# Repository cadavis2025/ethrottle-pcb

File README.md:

## FALSTAD Link
https://tinyurl.com/2aynfxed

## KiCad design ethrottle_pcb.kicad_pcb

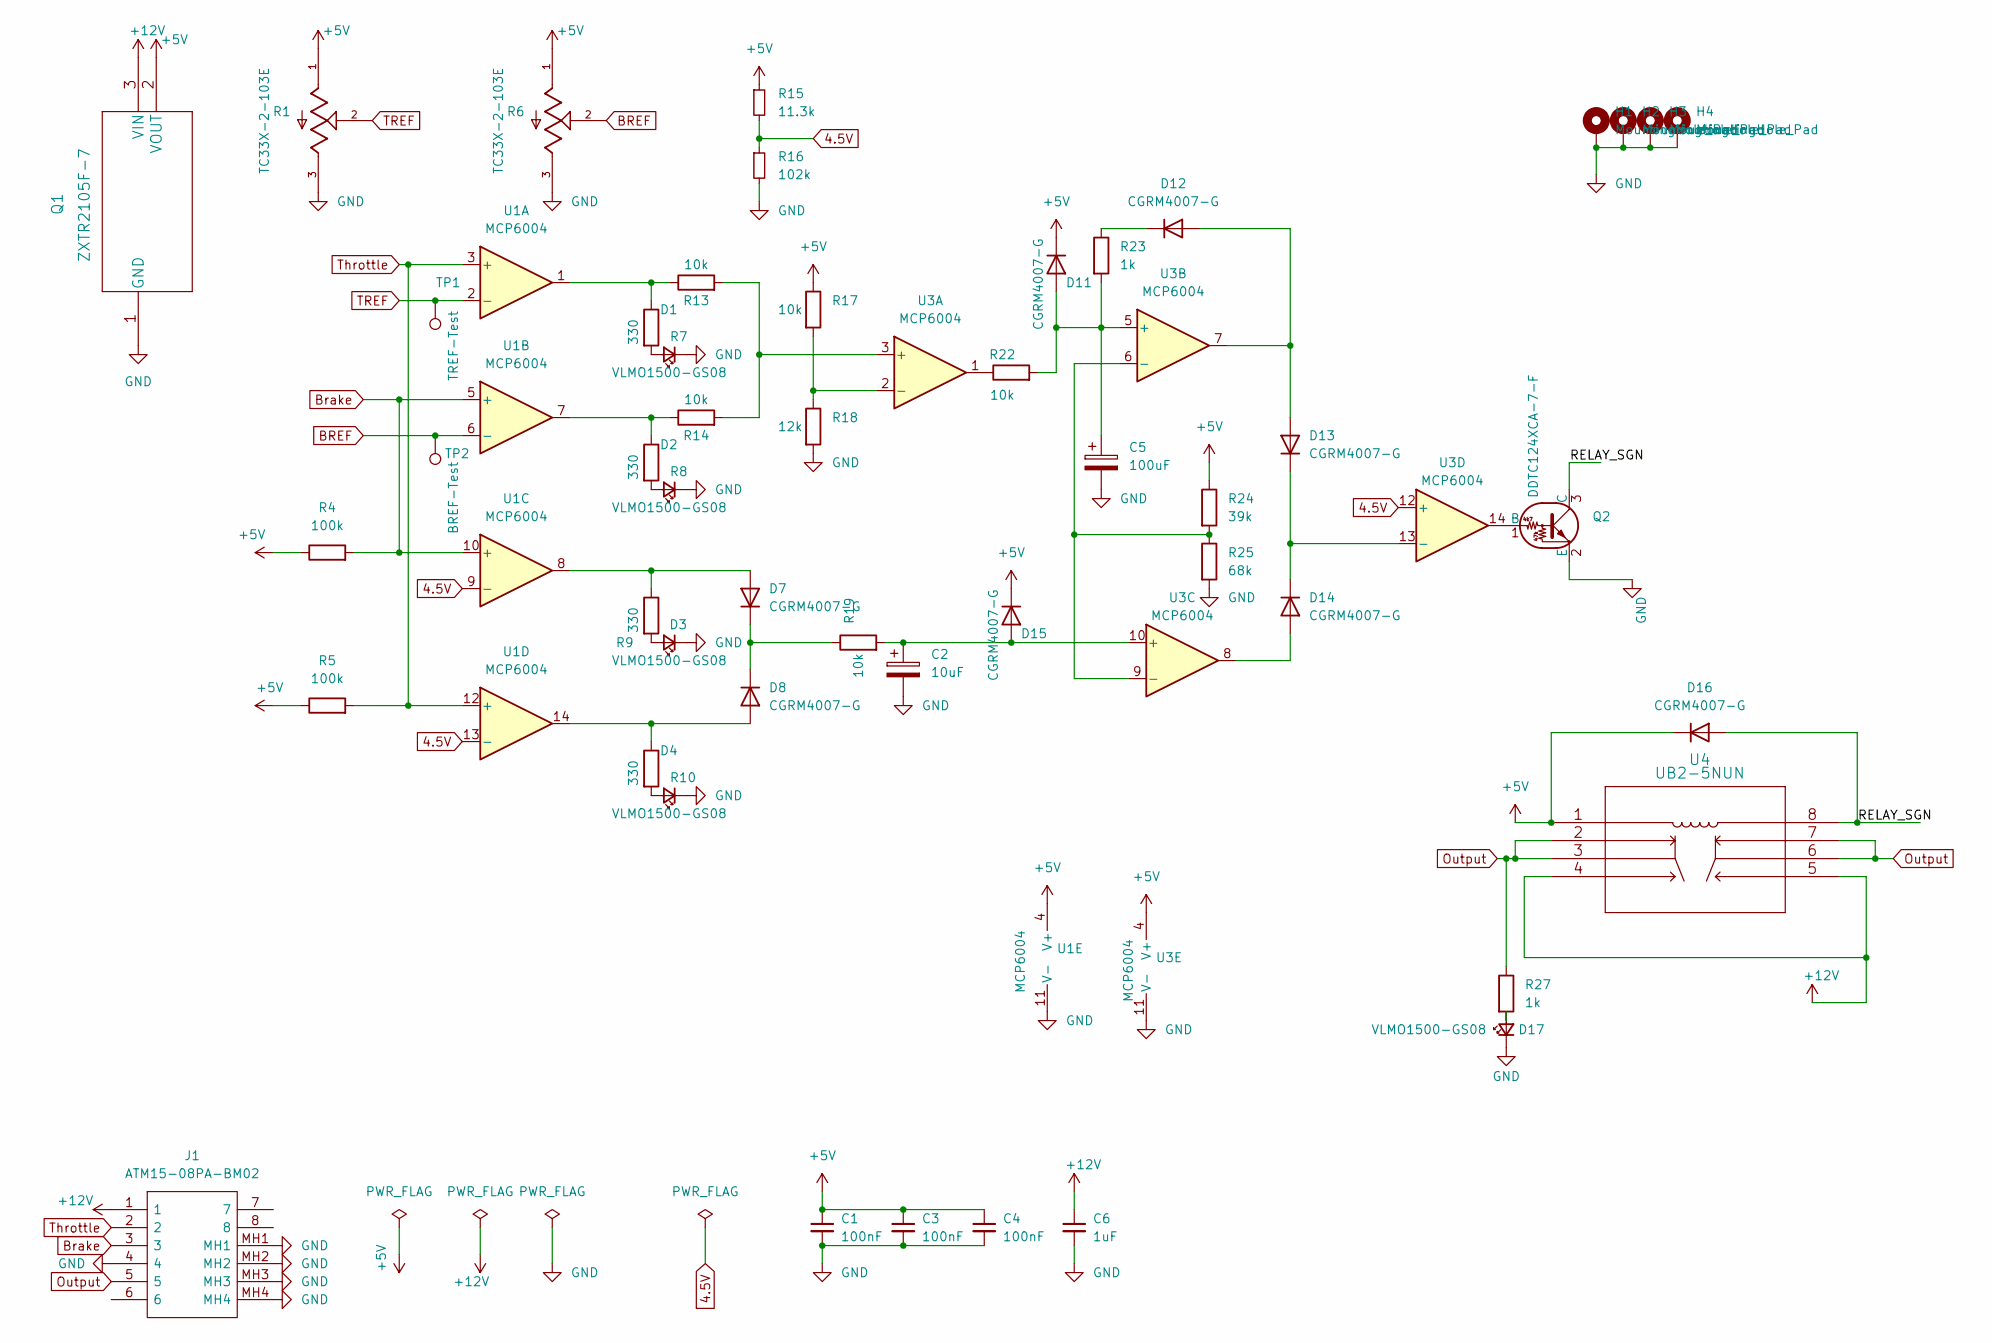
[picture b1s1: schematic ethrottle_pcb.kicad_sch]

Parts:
C1, C3, C4: 100nF; C_0603_1608Metric
C2: 10uF; C_0805_2012Metric
C5: 100uF; C_0805_2012Metric
C6: 1uF; C_0603_1608Metric
D1, D2, D3, D4, D17: VLMO1500-GS08; LED_0402_1005Metric
D7, D8, D11, D12, D13, D14, D15, D16: CGRM4007-G; D_SOD-123
H1, H2, H3, H4: MountingHole_Pad; MountingHole_3.5mm_Pad
J1: ATM15-08PA-BM02; ATM1508PABM02; Manufacturer_Part_Number ATM15-08PA-BM02; Mouser Part Number 654-ATM15-08PA-BM02
Q1: ZXTR2105F-7
Q2: DDTC124XCA-7-F; SOT-23
R1, R6: TC33X-2-103E; TRIM_TC33X-2-103E
R4, R5: 100k; R_0402_1005Metric
R7, R8, R9, R10: 330; R_0402_1005Metric
R13, R14, R17, R19, R22: 10k; R_0402_1005Metric
R15: 11.3k; R_0402_1005Metric
R16: 102k; R_0402_1005Metric
R18: 12k; R_0402_1005Metric
R23, R27: 1k; R_0402_1005Metric
R24: 39k; R_0402_1005Metric
R25: 68k; R_0402_1005Metric
TP1: TREF-Test; TestPoint_Plated_Hole_D2.0mm
TP2: BREF-Test; TestPoint_Plated_Hole_D2.0mm
U1, U3: MCP6004; SOP65P640X120-14N
U4: UB2-5NUN

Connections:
4.5V: R15.2, R16.1, U1.9 (-), U1.13 (-), U3.12 (+)
+5V: C1.1, C3.1, C4.1, D11.1 (K), D15.1 (K), D16.1 (K), Q1.2 (VOUT), R1.1, R4.1, R5.1, R6.1, R15.1, R17.1, R24.1, U1.4 (V+), U3.4 (V+), U4.1
+12V: C6.1, J1.1, Q1.3 (VIN), U4.4, U4.5
/RELAY_SGN: D16.2 (A), Q2.3 (C), U4.8
BREF: R6.2, TP2.1, U1.6 (-)
Brake: J1.3, R4.2, U1.5 (+), U1.10 (+)
GND: C1.2, C2.2, C3.2, C4.2, C5.2, C6.2, D1.1 (K), D2.1 (K), D3.1 (K), D4.1 (K), D17.1 (K), H1.1, H2.1, H3.1, H4.1, J1.4, J1.MH1, J1.MH2, J1.MH3, J1.MH4, Q1.1 (GND), Q2.2 (E), R1.3, R6.3, R16.2, R18.2, R25.2, U1.11 (V-), U3.11 (V-)
unnamed: D1.2 (A), R7.2
unnamed: D2.2 (A), R8.2
unnamed: D3.2 (A), R9.2
unnamed: D4.2 (A), R10.2
unnamed: D7.2 (A), R9.1, U1.8
unnamed: D7.1 (K), D8.1 (K), R19.1
unnamed: D8.2 (A), R10.1, U1.14
unnamed: C5.1, D11.2 (A), R22.2, R23.2, U3.5 (+)
unnamed: D12.2 (A), D13.2 (A), U3.7
unnamed: D12.1 (K), R23.1
unnamed: D13.1 (K), D14.1 (K), U3.13 (-)
unnamed: D14.2 (A), U3.8
unnamed: C2.1, D15.2 (A), R19.2, U3.10 (+)
unnamed: D17.2 (A), R27.2
unnamed: Q2.1 (B), U3.14
unnamed: R7.1, R13.1, U1.1
unnamed: R8.1, R14.1, U1.7
unnamed: R22.1, U3.1
unnamed: R13.2, R14.2, U3.3 (+)
unnamed: R17.2, R18.1, U3.2 (-)
unnamed: R24.2, R25.1, U3.6 (-), U3.9 (-)
Output: J1.5, R27.1, U4.2, U4.3, U4.6, U4.7
TREF: R1.2, TP1.1, U1.2 (-)
Throttle: J1.2, R5.2, U1.3 (+), U1.12 (+)

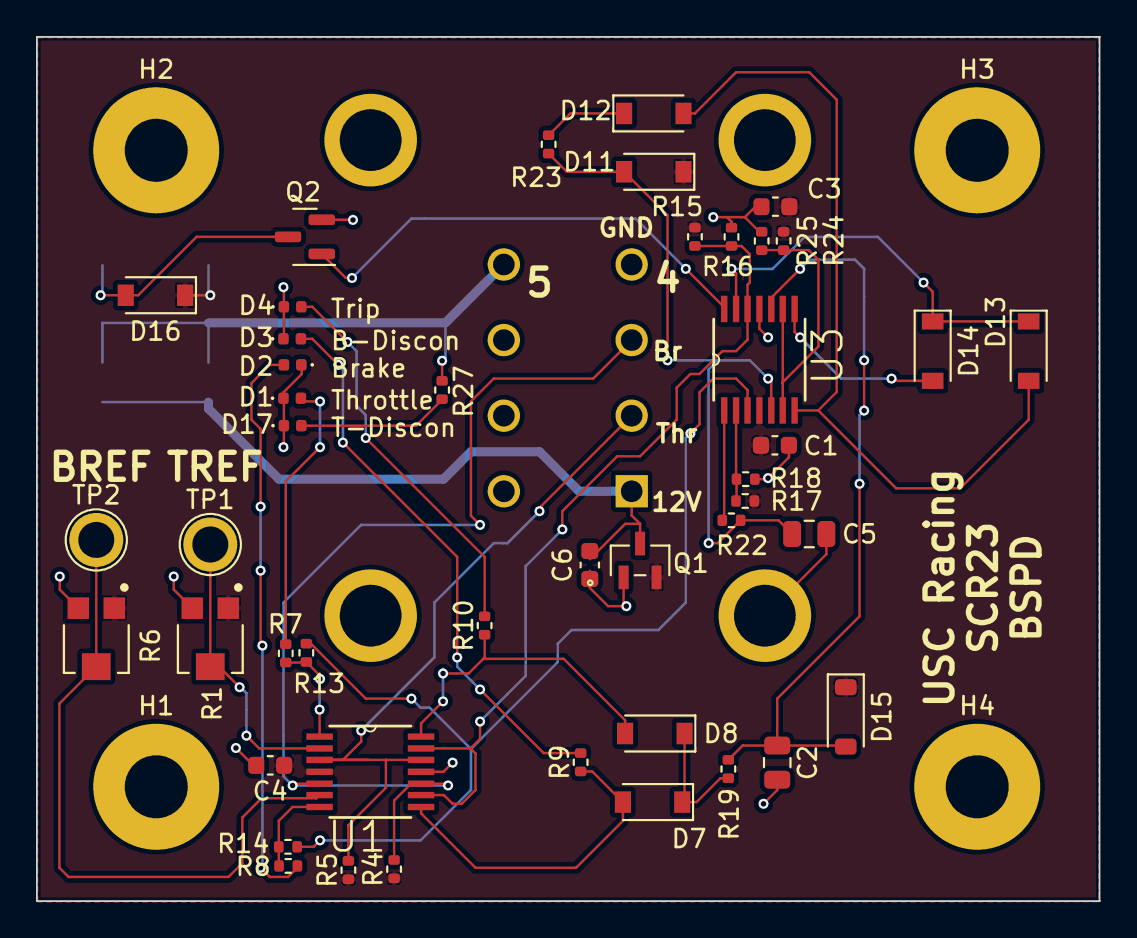
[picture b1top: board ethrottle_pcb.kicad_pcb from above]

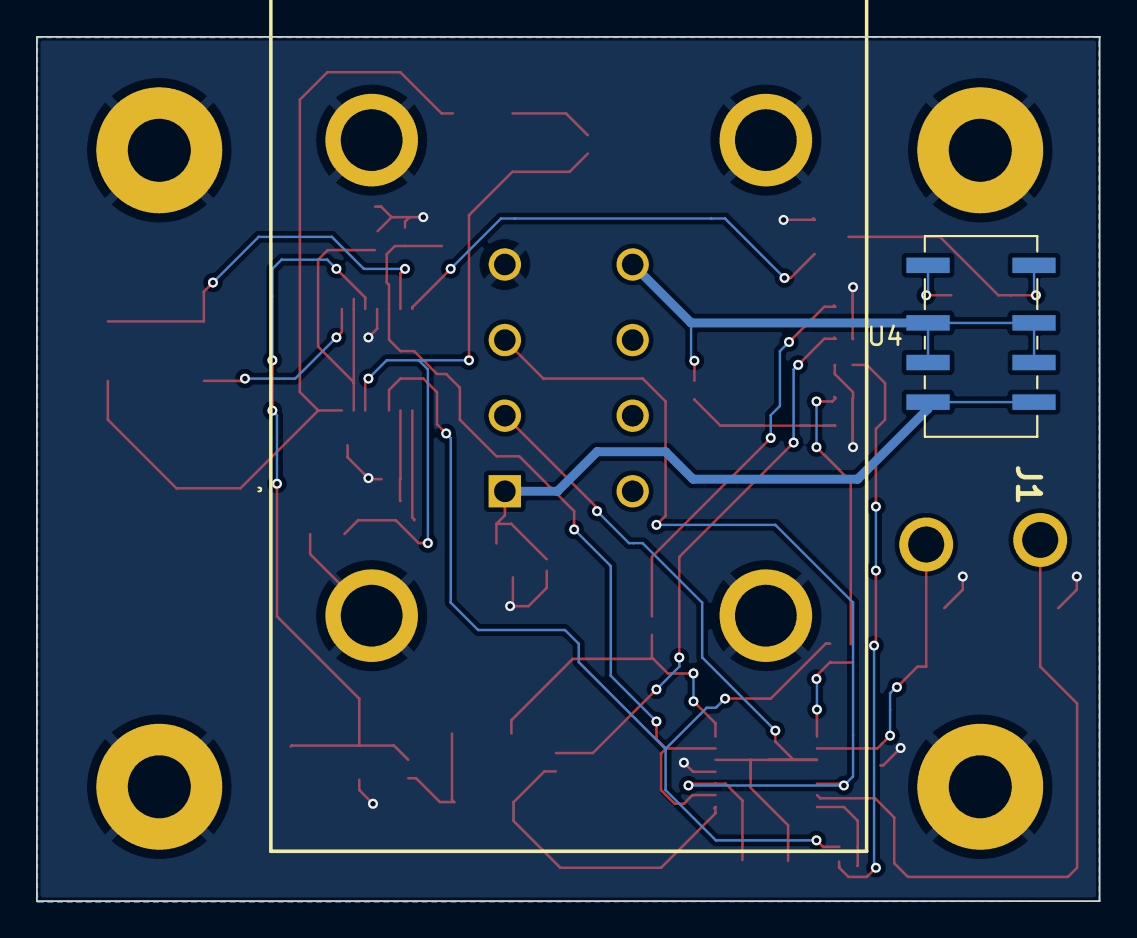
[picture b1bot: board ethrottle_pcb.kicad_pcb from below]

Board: 2 copper layers, 59.0 x 48.0 mm, 51 parts (2 on the bottom side), 31 nets.

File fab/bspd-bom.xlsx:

Id | Designator | Footprint | Quantity | Designation | Supplier and ref | Column1 | _1
1 | R15,R21 | R_01005_0402Metric | 2 | 11.3k
2 | R5,R2,R4,R3 | R_01005_0402Metric | 4 | 100k
3 | R12,R9,R11,R7,R10,R8 | R_01005_0402Metric | 6 | 330
4 | R25 | R_01005_0402Metric | 1 | 68k
5 | C1,C3,C4 | C_0201_0603Metric | 3 | 100nF
6 | D16,D12,D7,D10,D8,D11,D9,D14,D13 | D_SOD-123 | 9 | CGRM4007-G | https://www.comchiptech.com/admin/files/product/CGRM4004-G%2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
7 | R18 | R_01005_0402Metric | 1 | 12k
8 | R16,R20 | R_01005_0402Metric | 2 | 102k
9 | C2 | C_0805_2012Metric | 1 | 10uF | https://www.mouser.com/datasheet/2/40/AVXC_S_A0011956880_1-2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
10 | R13,R22,R19,R14,R17 | R_01005_0402Metric | 5 | 10k
11 | C5 | C_0805_2012Metric | 1 | 100uF | https://www.mouser.com/datasheet/2/40/AVXC_S_A0011956880_1-2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
12 | R24 | R_01005_0402Metric | 1 | 39k
13 | H3,H4,H1,H2 | MountingHole_3.5mm_Pad | 4 | MountingHole_Pad
14 | TP2 | TestPoint_Plated_Hole_D2.0mm | 1 | BREF-Test
15 | D6,D5,D4,D1,D2,D3 | LED_0402_1005Metric | 6 | LED | https://www.vishay.com/docs/82554/vlmo1500.pdf
16 | Q1 | ZXTR2105F-7 | 1 | ZXTR2105F-7 | https://www.mouser.com/datasheet/2/115/ZXTR2105F-1594562.pdf
17 | U1,U2,U3 | SOP65P640X120-14N | 3 | MCP6004 | https://ww1.microchip.com/downloads/en/DeviceDoc/MCP6001-1R-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
18 | TP1 | TestPoint_Plated_Hole_D2.0mm | 1 | TREF-Test
19 | R6,R1 | TRIM_TC33X-2-103E | 2 | TC33X-2-103E | https://www.bourns.com/docs/Product-Datasheets/TC33.pdf
20 | Q2 | SOT-23 | 1 | DDTC124XCA-7-F | https://www.diodes.com/assets/Datasheets/ds30330.pdf
21 | D17 | LED_0402_1005Metric | 1 | VLMO1500-GS08 | https://www.mouser.com/ProductDetail/Vishay-Semiconductors/V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
22 | C6 | C_0201_0603Metric | 1 | 1uF
23 | R23,R27 | R_01005_0402Metric | 2 | 1k
24 | U4 | UB2-5NUN | 1 | UB2-5NUN
25 | J1 | ATM1508PABM02 | 1 | ATM15-08PA-BM02

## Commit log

2022-10-07 updating labels & footprints
2022-10-07 updating symbol
2022-10-07 update labels
2022-10-07 update connections
2022-10-07 update footprints
2022-10-07 entire project
2022-10-11 add footprints
2022-10-18 layout in progress
2022-10-20 update format
2022-10-21 change labels
2022-10-23 add lm358
2022-10-25 add potentiometer
2022-10-25 add TREF/BREF
2022-10-25 adjust layout
2022-10-25 update constraints & layout
2022-10-25 some tracess
2022-10-25 fills & routing
2022-10-25 routes
2022-10-26 update constraints
2022-10-26 more traces
2022-10-26 0 unconnected
2022-10-26 prl file update
2022-11-03 updated schematic, not pcb
2022-11-04 layout changes
2022-11-14 finished routing
2022-11-15 layout edits
2022-11-15 adjust traces
2022-11-17 silkscreen
2022-11-18 small change
2022-11-18 add decoupling capacitor
2023-01-18 change d11 to 5v from 12v, add bjt for relay, lots of layout changes
2023-01-19 move relay to bottom, increase 12v rail trace thickness, various ancillary layout changes
2023-01-19 add NX assembly and step
2023-01-19 added all 3d models
2023-01-21 changed latching RC circuit to 10k and 100uF, basically the leakage current of d11 might self trip the circuit after some time
2023-02-09 change led
2023-02-09 add led indicator
2023-02-18 updated to kicad 7, modified layout of LEDs, sent pcb assembly out for audit
2023-02-18 add a couple files that couldn't be added since i had excel open
2023-02-28 skjgbsagdg
2023-02-28 fix the headass centroid files I forgot to specify some components as SMD so they didn't get exported
2023-03-19 add html iBOM
2023-09-06 add diode, remove unnecessary elements
2024-04-12 updated to kicad 8 and moved a bunch of silkscreens around, not sure why but all the project libraries are gone?
2024-04-12 sent for order
2024-04-17 made a folder for the one with ultra tiny capacitors
2024-04-17 made all the caps and resistors bigger because they were stupid small
2024-11-06 fix that LED
2024-11-06 add a readme with the falstad link

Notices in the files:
parts and their libraries:
Copyright 2021 Accelerated Designs. All rights reserved.
